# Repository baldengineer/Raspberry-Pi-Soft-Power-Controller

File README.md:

# Raspberry-Pi-Soft-Power-Controller

For now, you can find more information at:
https://hackaday.io/project/21625-raspberry-pi-soft-power-controller

## Requirements
* Raspberry Pi running Jessie
* 2 GPIO Pins on Raspberry Pi
* AVR (Arduino Uno, Leonardo, etc) w/ 2 GPIO
* Slide Switch (or Pushbutton)

### Optional
* Bald Engineer's RetroPie Controller

## Notes
* Currently the AVR code is designed for a SPST switch and not a push button. I'm working on a push button version, but that isn't what I needed in my project. 
* Please don't fab the PCBs as-is. There are design issues for them. I am open to collaboration on a "hat" version of these boards. I have some ideas. (Key, can we mount a barrel jack upside down??)

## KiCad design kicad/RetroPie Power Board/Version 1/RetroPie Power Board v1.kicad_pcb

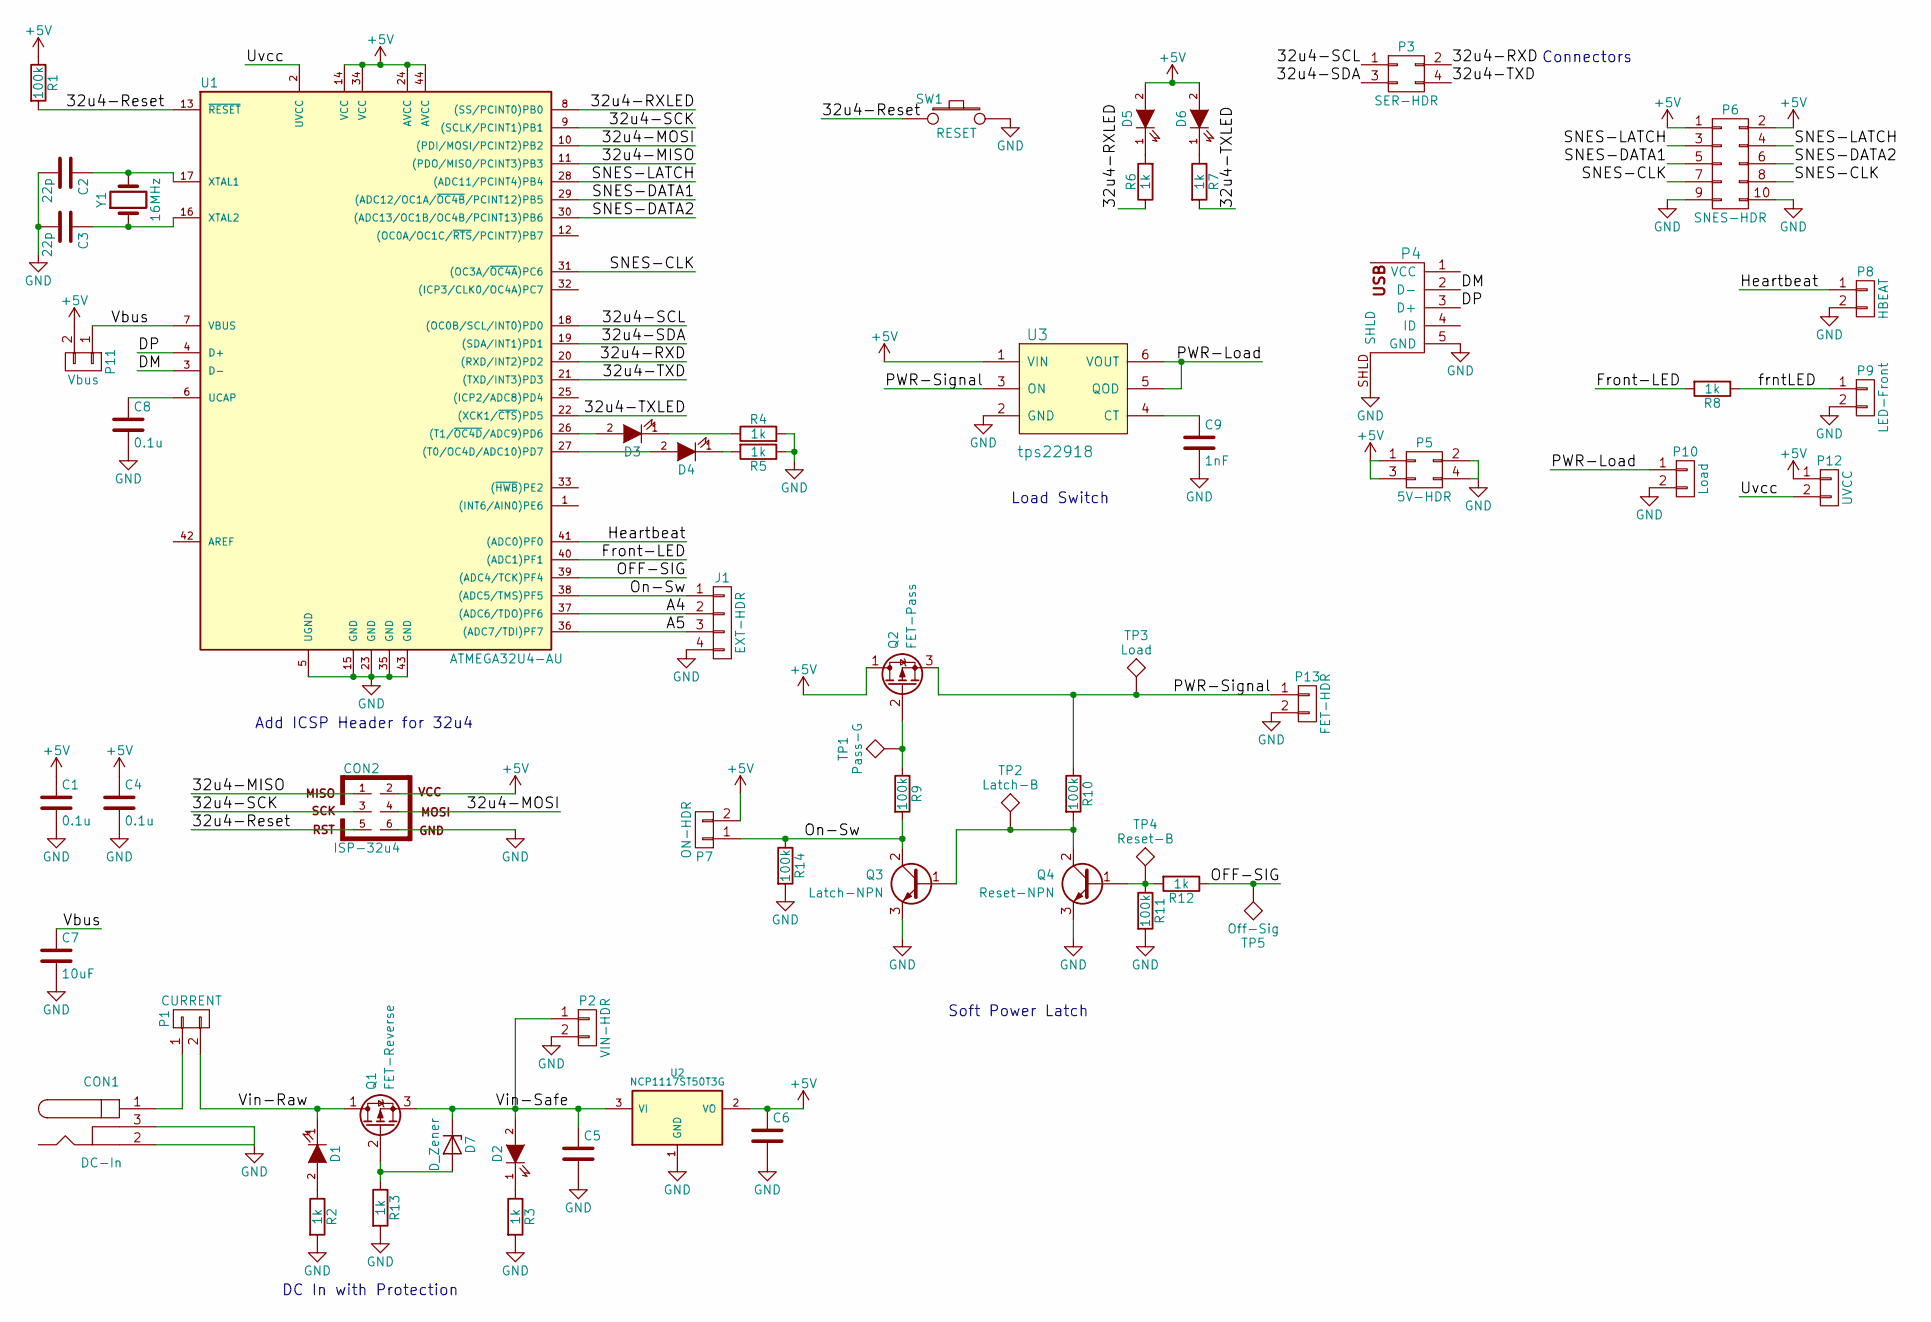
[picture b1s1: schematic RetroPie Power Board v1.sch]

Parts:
C1, C4: 0.1u; C_1206
C2, C3: 22p; C_1206
C5: CAP 47uF Polymer 10V; c_elec_5x5.3; Mouser PN 710-875105242006
C6: CAP 10uF Polymer 16V; c_elec_5x5.3; Mouser PN 710-875105359001
C7: 10uF; C_1206
C8: 0.1u; C_1206; Mouser PN 80-C1206C106K9PACTM
C9: 1nF; C_1206
CON1: DC-In; POWER_JACK_PTH
CON2: ISP-32u4; 2X03
D1: REV-RED; LED-1206
D2: GRN-PWRGD; LED-1206
D3: 32u4-LED1; LED-1206
D4: 32u4-LED2; LED-1206
D5: RXLED; LED-1206
D6: TXLED; LED-1206
D7: D_Zener; SOD-323_HandSoldering; Mouser PN 755-TFZVTR12B
J1: EXT-HDR; 1X04
P1: CURRENT; Pin_Header_Straight_1x02
P2: VIN-HDR; Pin_Header_Straight_1x02
P3: SER-HDR; Pin_Header_Straight_2x02
P4: USB_5PIN_SHELL; USB-MICRO_TH_4PEGS
P5: 5V-HDR; Pin_Header_Straight_2x02
P6: SNES-HDR; Pin_Header_Straight_2x05
P7: ON-HDR; Pin_Header_Straight_1x02
P8: HBEAT; Pin_Header_Straight_1x02
P9: LED-Front; Pin_Header_Straight_1x02
P10: Load; Pin_Header_Straight_1x02
P11: Vbus; Pin_Header_Straight_1x02
P12: UVCC; Pin_Header_Straight_1x02
P13: FET-HDR; Pin_Header_Straight_1x02
Q1: FET-Reverse; SOT-323; Mouser PN 863-MCH3383-TL-H
Q2: FET-Pass; SOT-323; Mouser PN 863-MCH3383-TL-H
Q3: Latch-NPN; SOT-23; Mouser PN 863-MMBT2222ALT1G
Q4: Reset-NPN; SOT-23; Mouser PN 863-MMBT2222ALT1G
R1, R9, R10, R11, R14: 100k; R_1206
R2, R3, R4, R5, R6, R7, R8, R12, R13: 1k; R_1206
SW1: RESET; SW_PUSHBUTTON_SMD
TP1: Pass-G; SolderWirePad_single_1-5mmDrill
TP2: Latch-B; SolderWirePad_single_1-5mmDrill
TP3: Load; SolderWirePad_single_1-5mmDrill
TP4: Reset-B; SolderWirePad_single_1-5mmDrill
TP5: Off-Sig; SolderWirePad_single_1-5mmDrill
U1: ATMEGA32U4-AU; QFP80P1200X1200X120-44N
U2: NCP1117ST50T3G; SOT223
U3: tps22918; SOT23-6
Y1: 16MHz; CRYSTAL_HC49_SMD

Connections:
+5V: C1.1, C4.1, C6.1, CON2.2, D5.2 (A), D6.2 (A), P5.1, P5.3, P6.1, P6.2, P7.2, P11.2, P12.1, Q2.1 (D), R1.1, U1.14 (VCC), U1.24 (AVCC), U1.34 (VCC), U1.44 (AVCC), U2.2 (VO), U3.1 (VIN)
/32u4-MISO: CON2.1, U1.11 ((PDO/MISO/PCINT3)PB3)
/32u4-MOSI: CON2.4, U1.10 ((PDI/MOSI/PCINT2)PB2)
/32u4-RXD: P3.2, U1.20 ((RXD/INT2)PD2)
/32u4-RXLED: R6.1, U1.8 ((SS/PCINT0)PB0)
/32u4-Reset: CON2.5, R1.2, SW1.1, U1.13 (~RESET~)
/32u4-SCK: CON2.3, U1.9 ((SCLK/PCINT1)PB1)
/32u4-SCL: P3.1, U1.18 ((OC0B/SCL/INT0)PD0)
/32u4-SDA: P3.3, U1.19 ((SDA/INT1)PD1)
/32u4-TXD: P3.4, U1.21 ((TXD/INT3)PD3)
/32u4-TXLED: R7.2, U1.22 ((XCK1/~CTS~)PD5)
/A4: J1.2, U1.37 ((ADC6/TDO)PF6)
/A5: J1.3, U1.36 ((ADC7/TDI)PF7)
/DM: P4.2 (D-), U1.3 (D-)
/DP: P4.3 (D+), U1.4 (D+)
/Front-LED: R8.2, U1.40 ((ADC1)PF1)
/Heartbeat: P8.1, U1.41 ((ADC0)PF0)
/OFF-SIG: R12.1, TP5.1, U1.39 ((ADC4/TCK)PF4)
/On-Sw: J1.1, P7.1, Q3.2 (C), R9.2, R14.1, U1.38 ((ADC5/TMS)PF5)
/PWR-Load: P10.1, U3.5 (QOD), U3.6 (VOUT)
/PWR-Signal: P13.1, Q2.3 (S), R10.1, TP3.1, U3.3 (ON)
/SNES-CLK: P6.7, P6.8, U1.31 ((OC3A/~OC4A~)PC6)
/SNES-DATA1: P6.5, U1.29 ((ADC12/OC1A/~OC4B~/PCINT12)PB5)
/SNES-DATA2: P6.6, U1.30 ((ADC13/OC1B/OC4B/PCINT13)PB6)
/SNES-LATCH: P6.3, P6.4, U1.28 ((ADC11/PCINT4)PB4)
/Uvcc: P12.2, U1.2 (UVCC)
/Vbus: C7.1, P11.1, U1.7 (VBUS)
/Vin-Raw: D1.1 (K), P1.2, Q1.1 (D)
/Vin-Safe: C5.1, D2.2 (A), D7.1 (K), P2.1, Q1.3 (S), U2.3 (VI)
/frntLED: P9.1, R8.1
GND: C1.2, C2.2, C3.2, C4.2, C5.2, C6.2, C7.2, C8.2, C9.2, CON1.2, CON1.3, CON2.6, J1.4, P2.2, P4.5 (GND), P4.SHLD, P5.2, P5.4, P6.9, P6.10, P8.2, P9.2, P10.2, P13.2, Q3.3 (E), Q4.3 (E), R2.2, R3.2, R4.2, R5.1, R11.2, R13.2, R14.2, SW1.2, U1.5 (UGND), U1.15 (GND), U1.23 (GND), U1.35 (GND), U1.43 (GND), U2.1 (GND), U3.2 (GND)
unnamed: C2.1, U1.17 (XTAL1), Y1.2
unnamed: C3.1, U1.16 (XTAL2), Y1.1
unnamed: C8.1, U1.6 (UCAP)
unnamed: C9.1, U3.4 (CT)
unnamed: CON1.1, P1.1
unnamed: D1.2 (A), R2.1
unnamed: D2.1 (K), R3.1
unnamed: D3.1 (K), R4.1
unnamed: D3.2 (A), U1.26 ((T1/~OC4D~/ADC9)PD6)
unnamed: D4.1 (K), R5.2
unnamed: D4.2 (A), U1.27 ((T0/OC4D/ADC10)PD7)
unnamed: D5.1 (K), R6.2
unnamed: D6.1 (K), R7.1
unnamed: D7.2 (A), Q1.2 (G), R13.1
unnamed: Q2.2 (G), R9.1, TP1.1
unnamed: Q3.1 (B), Q4.2 (C), R10.2, TP2.1
unnamed: Q4.1 (B), R11.1, R12.2, TP4.1

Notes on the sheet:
Soft Power Latch
Add ICSP Header for 32u4
DC In with Protection
Load Switch
Connectors

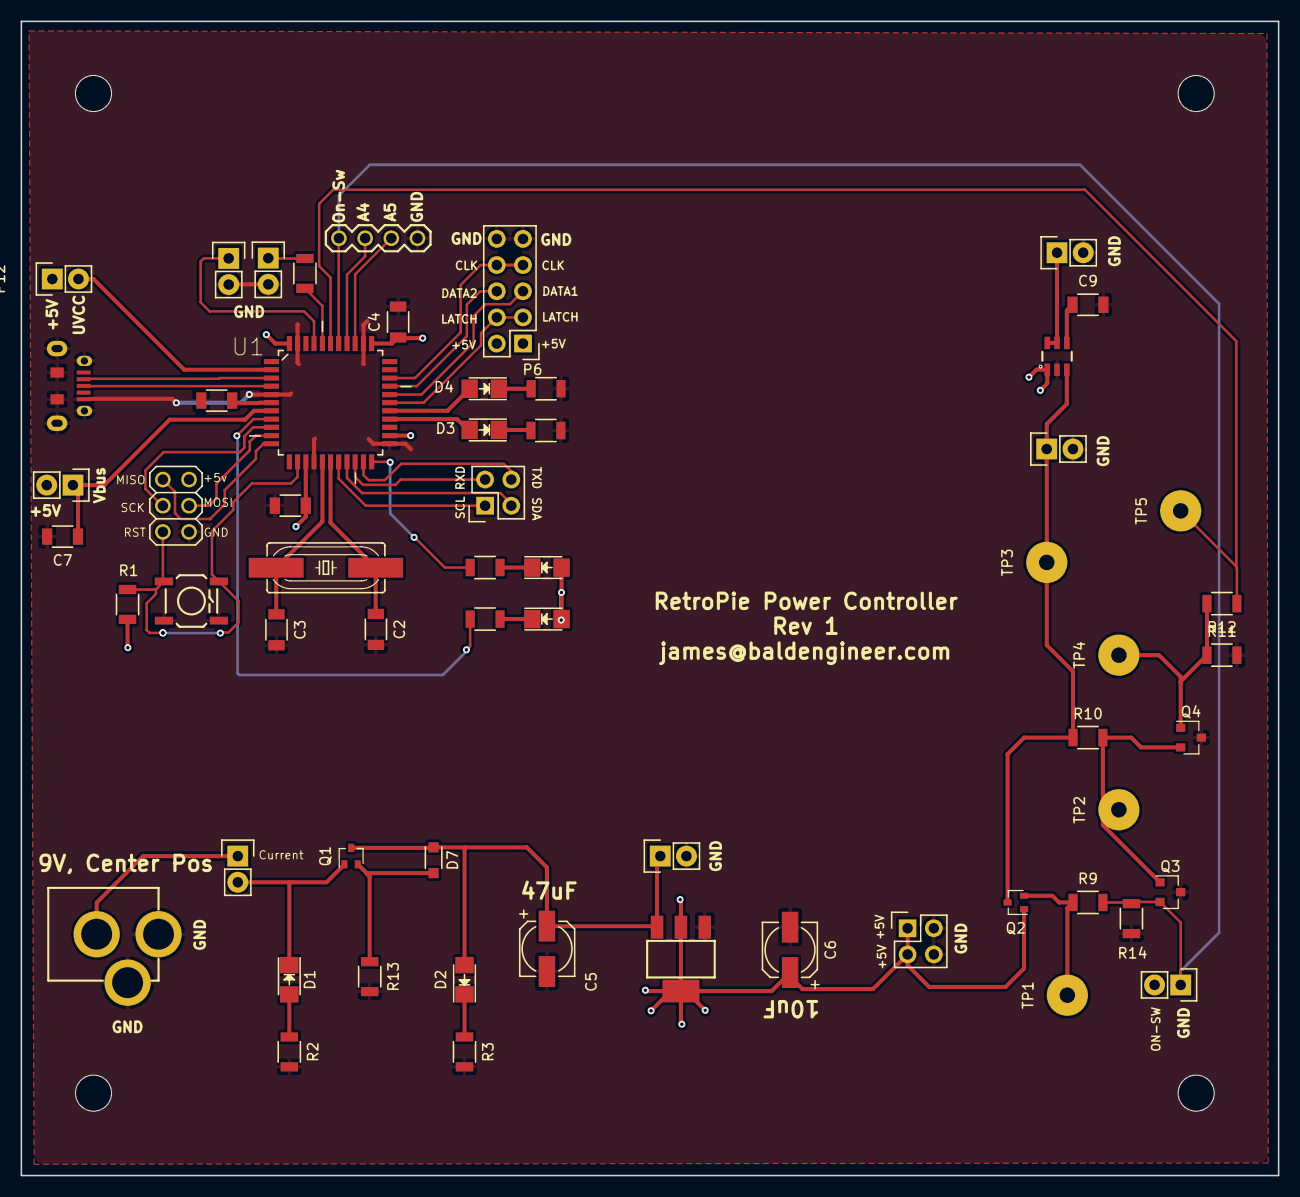
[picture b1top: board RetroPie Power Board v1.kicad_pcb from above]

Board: 2 copper layers, 122.0 x 112.0 mm, 60 parts (0 on the bottom side), 48 nets.

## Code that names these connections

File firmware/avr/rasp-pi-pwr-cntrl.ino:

//retropie-pwr-cntrl-v4.ino
// This code expects a SPST slide switch
// For more information, visit baldengineer.com and search "SNES"
// Code is still a work in progress

const byte signalFromPi = 3;  //PD0 is SCL
//const byte switchSense = 7;
const byte switchSense = A2;    //PF5
const byte offSignalPath = A3; //PF4 Verify: no additional Z, adc 4 on 32u4
const byte heartBeatLED = 6;  
const byte debugLED = 12;
const byte frontLED = A4;       // PF1 
const byte signalToPi = A5;// PF0 (is HeartBeat on Pi)
const byte extraA1 = A1;  // PF6, Mine: A4 - Actually A1
//const byte extraA0 = A0;  // PF7, Mine: A5 - Actually A0
const byte loadEnable = A1; // The Pi!
const byte switchLED = A0; // PD6

#define enableON HIGH
#define enableOFF LOW

unsigned long previousOFFSignalCount = millis();
unsigned long previousOFFSignalInterval = 1000;

unsigned long heartBeatPreviousMillis = millis();
unsigned long heartBeatInterval = 500;
bool heartBeatState = true;

unsigned long timerOffPreviousMillis = millis();
unsigned long timerOffInterval = 15000; 

unsigned long capDrainPreviousMillis = millis();
unsigned long capDrainInterval = 1000; 

unsigned long forcePowerOff = millis();
unsigned long forcePowerOffInterval = 45000UL; 
bool forcePowerOffState = false;

bool currentButtonState;
bool previousButtonState;

bool currentPiSignalState;
bool previousPiSignalState;

enum controllerStates {
	POWER_UP,
	BOOTING_PI,
	BOOTED,
	SHUT_DOWN_PI,
	POWER_DOWN
};
enum controllerStates controllerState = POWER_UP;
enum controllerStates previousControllerState = controllerState;

/*enum piPowerStates {
	OFF,
	BOOTING,
	BOOTED,
	SHUTTING_DOWN,
	KILLED
};
enum piPowerStates piPowerState = OFF;
enum piPowerStates previousPiPowerState = OFF; */

/*enum pwrButtonStates {
	UNKNOWN,
	SW_OFF,
	SW_ON,
	CHANGED
};
enum pwrButtonStates pwrButtonState = UNKNOWN;
enum pwrButtonStates previousPwrButtonState = UNKNOWN;*/


void setup() {
	Serial.begin(9600);	// debugging 
	pinMode(debugLED, OUTPUT);

	pinMode(offSignalPath, INPUT);

	pinMode(heartBeatLED, OUTPUT);
	pinMode(switchSense, INPUT);
	pinMode(signalFromPi, INPUT);

	pinMode(signalToPi, OUTPUT);
	digitalWrite(signalToPi, LOW);
	
	pinMode(loadEnable, OUTPUT);
	digitalWrite(loadEnable, enableOFF);
}

void heartBeat(unsigned long millisTime) {
	if (millisTime - heartBeatPreviousMillis >= heartBeatInterval) {
		heartBeatPreviousMillis = millisTime;	
		heartBeatState = !heartBeatState;
		digitalWrite(heartBeatLED, heartBeatState);
	}
}


void stateDebug() {
	if (previousControllerState != controllerState) {
		Serial.println(controllerState);
		previousControllerState = controllerState;
	}
}

/*int processPiSignalChange(bool piState) {
	// save it, for some reason
	previousPiPowerState = piPowerState;
	if (piState)
		return BOOTED;
	else
		return SHUTTING_DOWN;
}

int processPwrButtonChange(bool buttonState) {
	pwrButtonState = previousPwrButtonState;
	if (buttonState)
		return CHANGED_TO_ON;
	else
		return CHANGED_TO_OFF;
}*/

void loop() {
	// blink the LED
	heartBeat(millis());

	// check where the Pi is at
	currentPiSignalState = digitalRead(signalFromPi);
	if (previousPiSignalState != currentPiSignalState) {
		// in case has some noise wait and re-sample
		delay(10);
		currentPiSignalState = digitalRead(signalFromPi);
		previousPiSignalState = currentPiSignalState;

		//piPowerState = processPiSignalChange(currentPiSignalState);
	} 

	// how is the button doing?
	currentButtonState = digitalRead(switchSense);
	if (previousButtonState != currentButtonState) {
		// in case of bounce, wait and re-sample
		delay(20);
		currentButtonState = digitalRead(switchSense);
		previousButtonState = currentButtonState;

		// let the Pi know if it should be on or off
		digitalWrite(signalToPi, currentButtonState);

		if (currentButtonState == LOW) {
			// user is forcing shutdown, so start emergency timer
			//timerOffPreviousMillis = millis(); 
			pinMode(offSignalPath, OUTPUT);
			digitalWrite(offSignalPath, HIGH);
			forcePowerOff = millis();
		}

		//pwrButtonState = processPwrButtonChange(currentButtonState);
		//pwrButtonState = CHANGED;
	}

	switch (controllerState) {
		case POWER_UP:
			stateDebug();
			// disable heart beat 
			heartBeatPreviousMillis = millis();
			heartBeatState = false;

			// should be a no brainer.
			if (currentButtonState) {
				//pwrButtonState = SW_ON;
				controllerState = BOOTING_PI;
			}	
		break;

		case BOOTING_PI:
			//stateDebug();
			heartBeatInterval = 1000;

			// Turn on the Pi
			digitalWrite(loadEnable, enableON);

			// wait for Pi to boot
			if (currentPiSignalState) {
				controllerState = BOOTED;
			}

			// kill the power if the Pi never boot (or we never)
			// get our PiAlive signal.
			if (currentButtonState == LOW) {
				capDrainPreviousMillis = millis();
				digitalWrite(signalToPi, LOW);
				controllerState = POWER_DOWN;
			}
		break;

		case BOOTED:
			//stateDebug();
			heartBeatInterval = 500;

			// wait for Pi signal that it is shutting down
			if (currentPiSignalState == LOW) {
				// Pi Initiated Shutdown
				timerOffPreviousMillis = millis();
				controllerState = SHUT_DOWN_PI;
			}

			if (currentButtonState == LOW) {
				// User is telling Pi to shut down.
				timerOffPreviousMillis = millis(); // moved to switch change
				//forcePowerOff = millis();
				controllerState = SHUT_DOWN_PI;
			} else {
				// let the swtich keep the cap up.
				pinMode(offSignalPath, INPUT);
			}


		break;

		case SHUT_DOWN_PI:
			//stateDebug();
			heartBeatInterval = 250;
			// give the Pi some time to finish up its power-down
			if (currentPiSignalState == LOW) {
				if (millis() - timerOffPreviousMillis >= timerOffInterval) {
					controllerState = POWER_DOWN;
					capDrainPreviousMillis = millis();
				}
			}

			// or a reboot is occured
			if (currentPiSignalState) {
				controllerState = BOOTED;
			}

			// Shutdown took way too long
			if (millis() - forcePowerOff >= forcePowerOffInterval) {
				controllerState = POWER_DOWN;
				capDrainPreviousMillis = millis();
			}
		break;

		case POWER_DOWN:
			//stateDebug();
			heartBeatInterval = 100;

			// let the cap drain once the switch goes off.
			if (currentButtonState == LOW) {
				// turn off the Pi
				digitalWrite(loadEnable, enableOFF);
				if (millis() - capDrainPreviousMillis >= capDrainInterval) {
					// drain the cap
					pinMode(offSignalPath, OUTPUT);
					digitalWrite(offSignalPath, LOW);
				}				
			}
		break;
	}
}

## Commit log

2017-05-01 first commit, it's probably broken.
2017-05-01 readme update
2017-05-03 Delete Zero Current Soft Power v2.kicad_pcb
    Really shouldn't have published this yet, since it is just a copy of V1. It doesn't fix any flaws yet.
2017-06-10 Major Update. New State Machine. Fixed systemd
2017-06-10 Added shutdown from controller.
2017-06-10 added shutdown from controller
2017-06-10 Added READMEs.
